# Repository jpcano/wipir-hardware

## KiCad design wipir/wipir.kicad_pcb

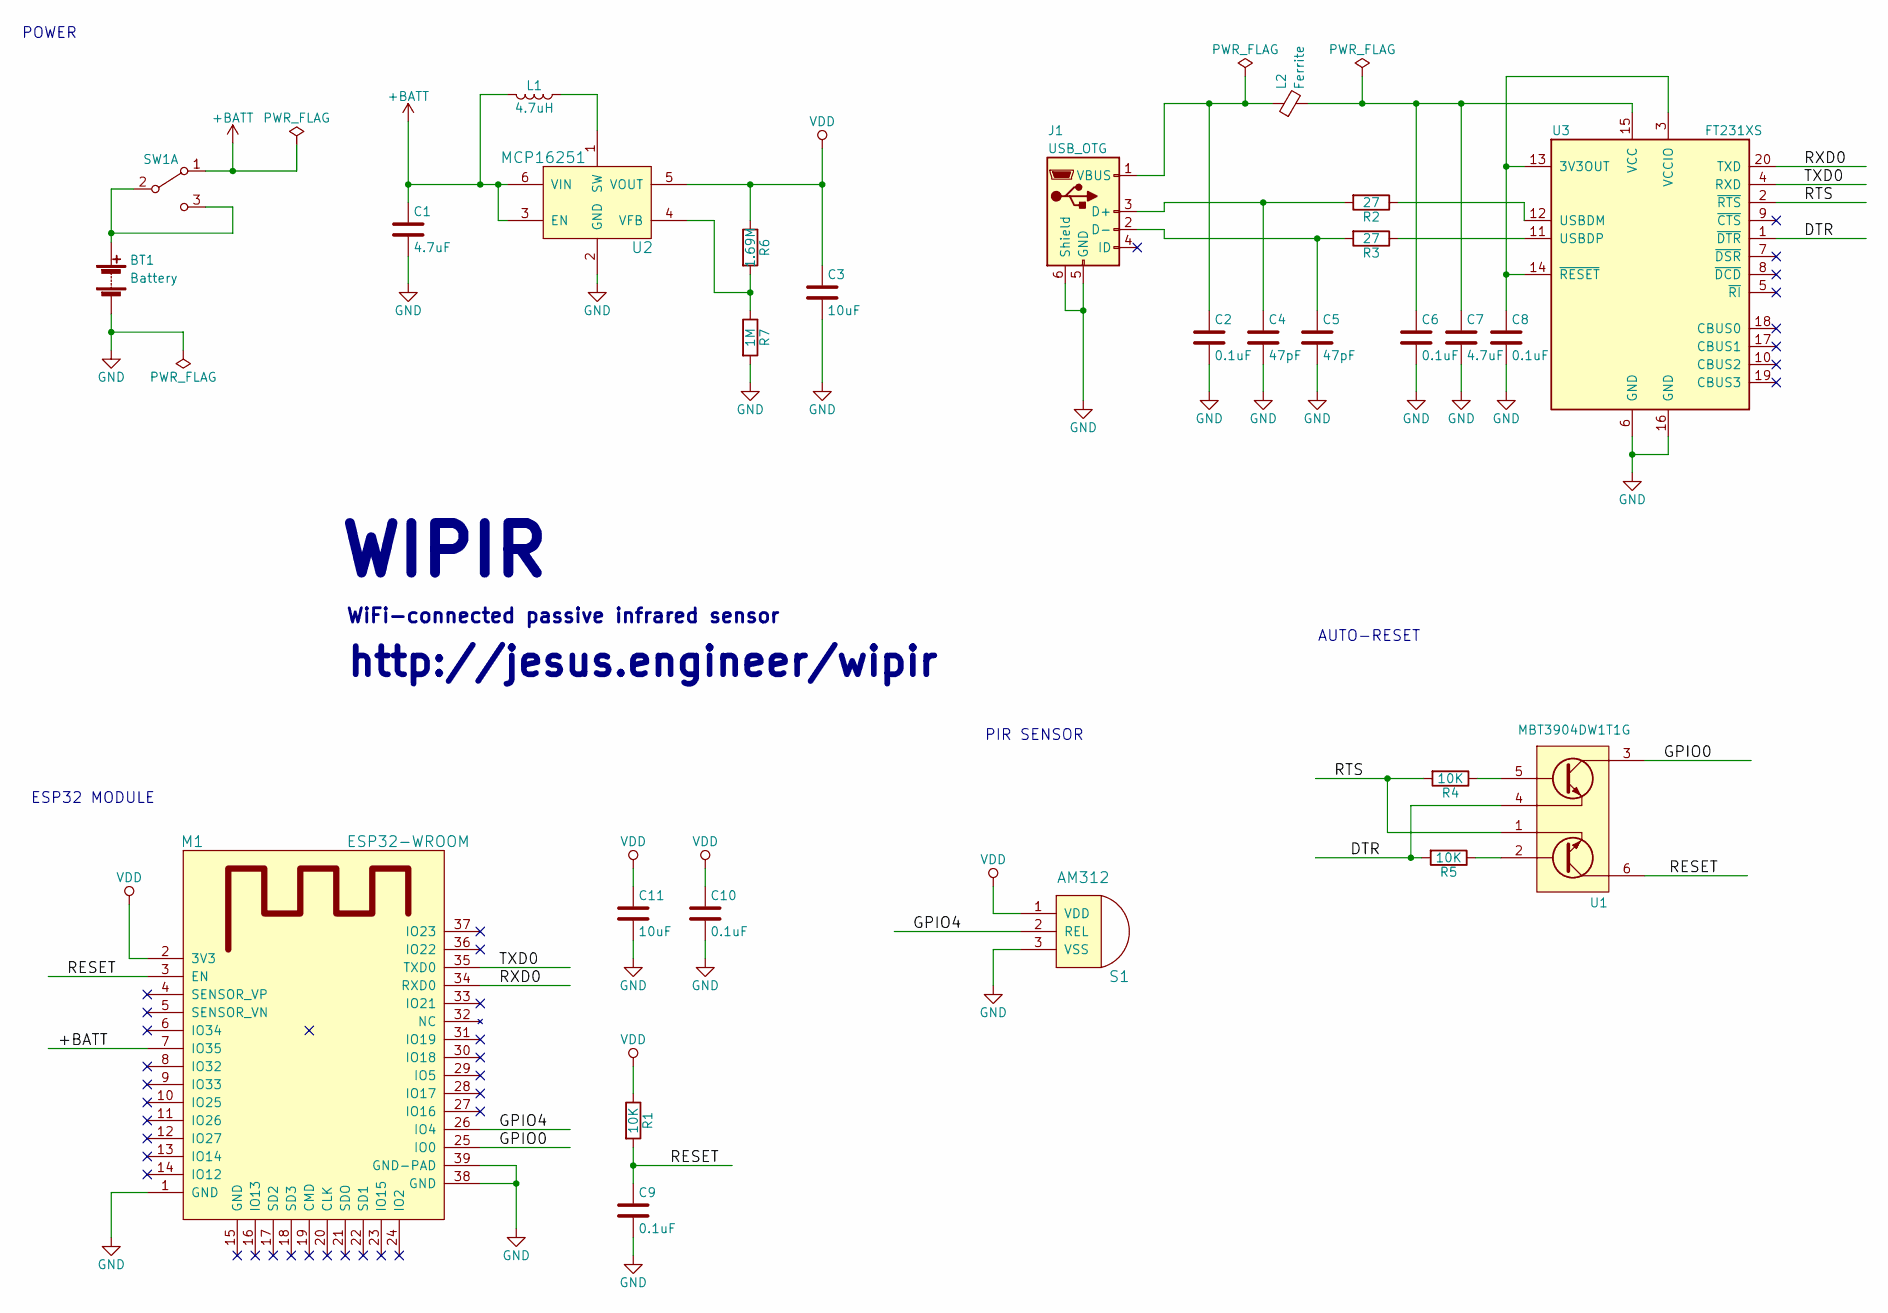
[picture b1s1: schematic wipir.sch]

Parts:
BT1: Battery; AAA-SINGL-CONTACT
C1, C7: 4.7uF; C_0603_HandSoldering
C2, C6, C8, C9, C10: 0.1uF; C_0603_HandSoldering
C3, C11: 10uF; C_0603_HandSoldering
C4, C5: 47pF; C_0603_HandSoldering
J1: USB_OTG; USB_Micro-B_Molex_47346-0001
L1: 4.7uH; VLS3015ET-4R7M
L2: Ferrite; L_0805_HandSoldering
M1: ESP32-WROOM
R1, R4, R5: 10K; R_0603_HandSoldering
R2, R3: 27; R_0603_HandSoldering
R6: 1.69M; R_0603_HandSoldering
R7: 1M; R_0603_HandSoldering
S1: AM312
SW1: SW_DPDT_x2; PCM12SMTR
U1: MBT3904DW1T1G; SOT-363_SC-70-6_Handsoldering
U2: MCP16251; SOT-23-6_Handsoldering
U3: FT231XS; SSOP-20

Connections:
+BATT: C1.1, L1.2, M1.7 (IO35), SW1.1 (A), U2.3 (EN), U2.6 (VIN)
/DTR: R5.2, U1.4, U3.1 (~DTR)
/GPIO0: M1.25 (IO0), U1.3
/GPIO4: M1.26 (IO4), S1.2 (REL)
/RESET: C9.1, M1.3 (EN), R1.2, U1.6
/RTS: R4.2, U1.1, U3.2 (~RTS)
/RXD0: M1.34 (RXD0), U3.20 (TXD)
/TXD0: M1.35 (TXD0), U3.4 (RXD)
GND: BT1.2 (-), C1.2, C2.2, C3.2, C4.2, C5.2, C6.2, C7.2, C8.2, C9.2, C10.2, C11.2, J1.5 (GND), J1.6 (Shield), M1.1 (GND), M1.38 (GND), M1.39 (GND-PAD), R7.2, S1.3 (VSS), U2.2 (GND), U3.6 (GND), U3.16 (GND)
unnamed: BT1.1 (+), SW1.2 (B), SW1.3 (C)
unnamed: C2.1, J1.1 (VBUS), L2.1
unnamed: C4.1, J1.3 (D+), R2.2
unnamed: C5.1, J1.2 (D-), R3.2
unnamed: C6.1, C7.1, L2.2, U3.15 (VCC)
unnamed: C8.1, U3.3 (VCCIO), U3.13 (3V3OUT), U3.14 (~RESET)
unnamed: L1.1, U2.1 (SW)
unnamed: R2.1, U3.12 (USBDM)
unnamed: R3.1, U3.11 (USBDP)
unnamed: R4.1, U1.5
unnamed: R5.1, U1.2
unnamed: R6.2, R7.1, U2.4 (VFB)
VDD: C3.1, C10.1, C11.1, M1.2 (3V3), R1.1, R6.1, S1.1 (VDD), U2.5 (VOUT)

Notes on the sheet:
POWER
PIR SENSOR
AUTO-RESET
ESP32 MODULE
http://jesus.engineer/wipir
WIPIR
WiFi-connected passive infrared sensor

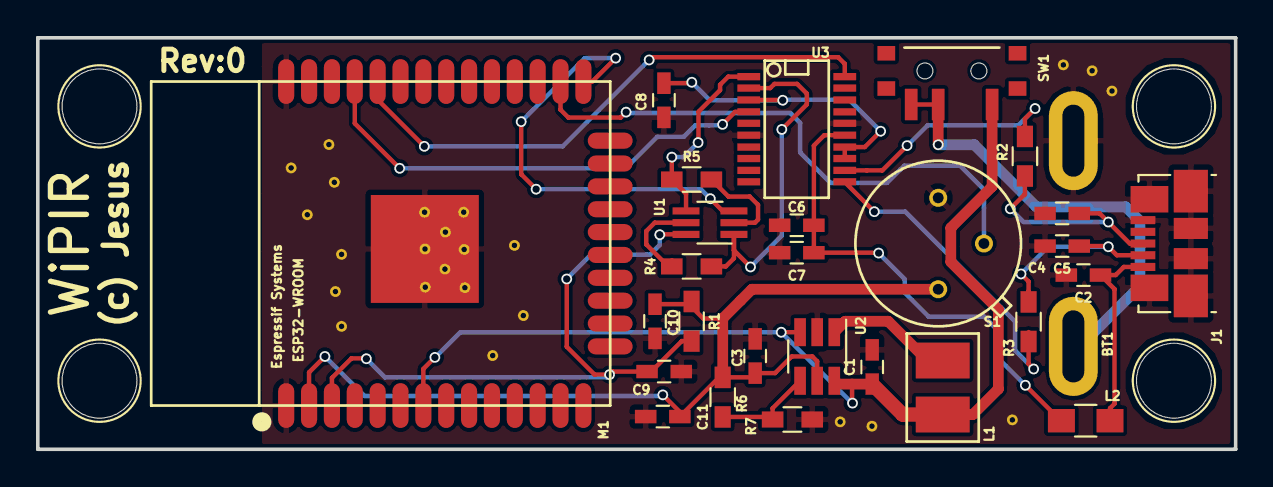
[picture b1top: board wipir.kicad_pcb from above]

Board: 2 copper layers, 66.5 x 22.9 mm, 28 parts (0 on the bottom side), 22 nets.
